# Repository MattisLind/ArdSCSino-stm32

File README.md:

# ArdSCSino-stm32

The idea and the base code was taken from a project created by Tambo (TNB Seisakusho) (https://twitter.com/h_koma2) ArdSCSino is hardware that reproduces SCSI devices (hard disks) with arduino.

### Setup

I am using Arduino Software (IDE) V1.8.13.
Tools-> Boards-> Board Manager-> Search Filters Search and install "Arduino SAM board (32-bit ARM Cortex-M3)" Select the board "Generic STM32F103C series"

I am using the following as a library.

SDFAT (https://github.com/greiman/SdFat/tree/1.1.4) 

* Make sure to use V1 of SdFat (for example V1.1.4 )
* Make sure to set the #define ENABLE_EXTENDED_TRANSFER_CLASS 1 in SdFatConfig.h

Arduino_STM32 (https://github.com/rogerclarkmelbourne/Arduino_STM32/releases/tag/v1.0.0)

## Enhancements

In the STM32SCSISD folder there is a new PCB which integrates the following features:
* Floppy / AMP / TE connectivity connector.
* Pin headers for serial port, USB, SWD connectors. The use of these are for debugging only and is purely optional.
* Jumpers for RESET and BOOT. Also only needed for debuging.
* Jumpers for and image select. The image select feature allow for selecting one out of four images on the card when the SCSI device is selected.
* Jumpers for unit select. Allow the settig of the SCSI ID. The ID is also used to select one of seven sets of images as defined by the image select above.
* Activity LED pin header.
* Mounting holes.

The firmware (in STM32SCSISD_FW) has been improved by optimizing how data is transfered to the SCSI port. One SCSI transaction is now 1.2 microsseconds and the innerloop consists of 30 instructions. Please make sure that you use -O3 optimizations when compiling the project.

```
arm-none-eabi-g++ -mcpu=cortex-m3 -mthumb ArdSCSinoV2.cpp ../../SdFat/src/FatLib/FatFile.cpp  -I../../Arduino_STM32/STM32F1/libraries/SPI/src/ -I../../Arduino_STM32/STM32F1/system/libmaple/include/ -I../../Arduino_STM32/STM32F1/system/libmaple/ -I../../Arduino_STM32/STM32F1/cores/maple/ -I../../Arduino_STM32/STM32F1/variants/generic_stm32f103c -DMCU_STM32F103C8 -I../../Arduino_STM32/STM32F1/system/libmaple/stm32f1/include/ -I../../SdFat/src/ -DARDUINO -DF_CPU=72000000 -D__arm__ -D__STM32F1__ -Dnullptr=NULL -O3
```

Real life copying of 5 Mbyte file under RT-11 operating system running on a PDP-11/23 CPU takes 23 seconds which is equivalent of 218kbytes/s copying speed. Comparing this with the SCSI2SD v5 adapter gives a 305kbytes/s copying speed. 

The design has also been tested successfully with a Luxor ABC1600 computer.

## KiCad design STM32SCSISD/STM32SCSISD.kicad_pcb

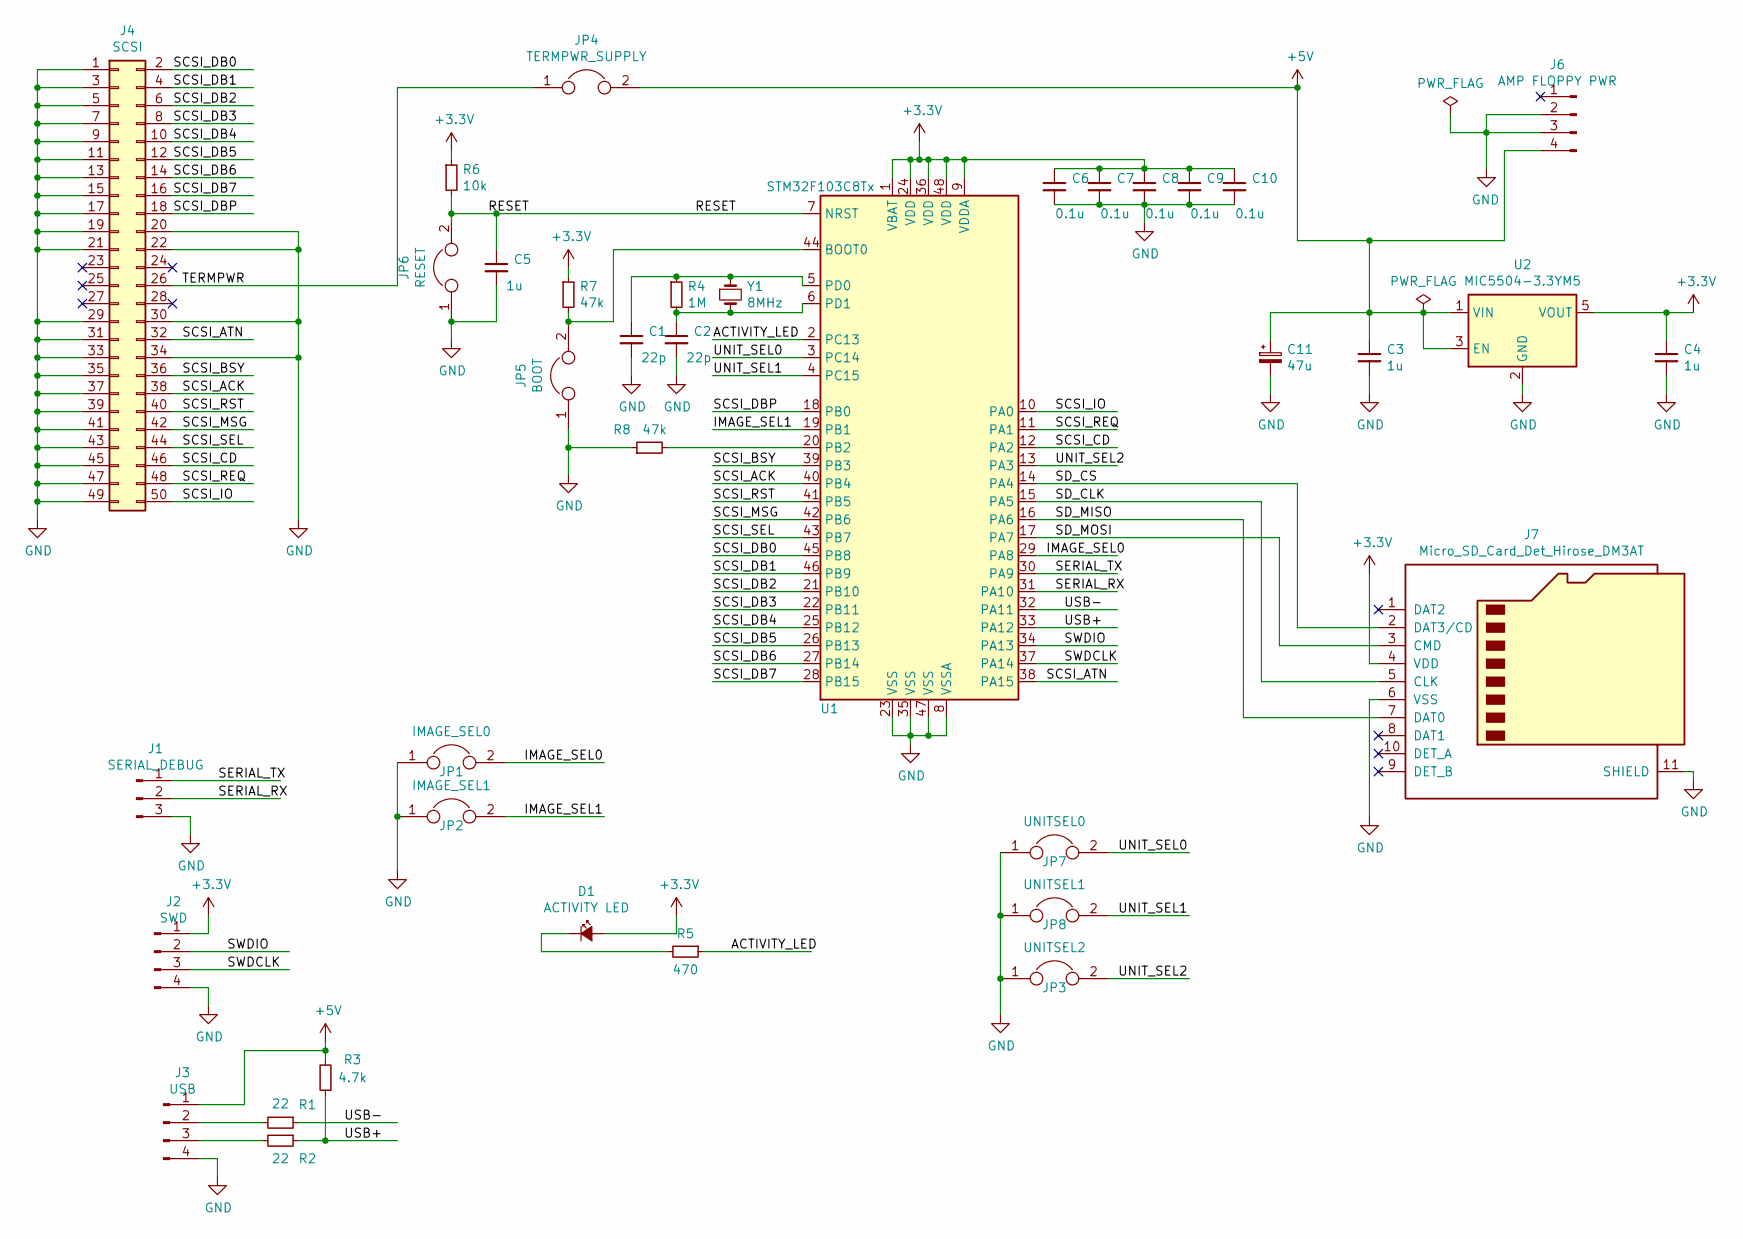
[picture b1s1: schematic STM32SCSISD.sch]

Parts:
C1, C2: 22p; C_0805_2012Metric
C3, C4, C5: 1u; C_0805_2012Metric
C6, C7, C8, C9, C10: 0.1u; C_0805_2012Metric
C11: 47u; CP_Radial_D5.0mm_P2.50mm
D1: ACTIVITY LED; LED_D5.0mm
J1: SERIAL_DEBUG; PinHeader_1x03_P2.54mm_Vertical
J2: SWD; PinHeader_1x04_P2.54mm_Vertical
J3: USB; PinHeader_1x04_P2.54mm_Vertical
J4: SCSI; IDC-Header_2x25_P2.54mm_Vertical
J6: AMP FLOPPY PWR; TE_MATE-N-LOK_350211-1_1x04_P5.08mm_Vertical
J7: Micro_SD_Card_Det_Hirose_DM3AT; microSD_HC_Hirose_DM3AT-SF-PEJM5
JP1: IMAGE_SEL0; PinHeader_1x02_P2.54mm_Vertical
JP2: IMAGE_SEL1; PinHeader_1x02_P2.54mm_Vertical
JP3: UNITSEL2; PinHeader_1x02_P2.54mm_Vertical
JP4: TERMPWR_SUPPLY; PinHeader_1x02_P2.54mm_Vertical
JP5: BOOT; PinHeader_1x02_P2.54mm_Vertical
JP6: RESET; PinHeader_1x02_P2.54mm_Vertical
JP7: UNITSEL0; PinHeader_1x02_P2.54mm_Vertical
JP8: UNITSEL1; PinHeader_1x02_P2.54mm_Vertical
R1, R2: 22; R_0805_2012Metric_Pad1.15x1.40mm_HandSolder
R3: 4.7k; R_0805_2012Metric_Pad1.15x1.40mm_HandSolder
R4: 1M; R_0805_2012Metric_Pad1.15x1.40mm_HandSolder
R5: 470; R_0805_2012Metric_Pad1.15x1.40mm_HandSolder
R6: 10k; R_0805_2012Metric_Pad1.15x1.40mm_HandSolder
R7, R8: 47k; R_0805_2012Metric_Pad1.15x1.40mm_HandSolder
U1: STM32F103C8Tx; LQFP-48_7x7mm_P0.5mm
U2: MIC5504-3.3YM5; SOT-23-5
Y1: 8MHz; Crystal_HC49-U_Vertical

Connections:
+3V3: C4.1, C6.1, C7.1, C8.1, C9.1, C10.1, D1.2 (A), J2.1, J7.4 (VDD), R6.1, R7.1, U1.1 (VBAT), U1.9 (VDDA), U1.24 (VDD), U1.36 (VDD), U1.48 (VDD), U2.5 (VOUT)
+5V: C3.1, C11.1, J3.1, J6.4, JP4.2, R3.2, U2.1 (VIN), U2.3 (EN)
/ACTIVITY_LED: R5.1, U1.2 (PC13)
/IMAGE_SEL0: JP1.2, U1.29 (PA8)
/IMAGE_SEL1: JP2.2, U1.19 (PB1)
/RESET: C5.1, JP6.2, R6.2, U1.7 (NRST)
/SCSI_ACK: J4.38, U1.40 (PB4)
/SCSI_ATN: J4.32, U1.38 (PA15)
/SCSI_BSY: J4.36, U1.39 (PB3)
/SCSI_CD: J4.46, U1.12 (PA2)
/SCSI_DB0: J4.2, U1.45 (PB8)
/SCSI_DB1: J4.4, U1.46 (PB9)
/SCSI_DB2: J4.6, U1.21 (PB10)
/SCSI_DB3: J4.8, U1.22 (PB11)
/SCSI_DB4: J4.10, U1.25 (PB12)
/SCSI_DB5: J4.12, U1.26 (PB13)
/SCSI_DB6: J4.14, U1.27 (PB14)
/SCSI_DB7: J4.16, U1.28 (PB15)
/SCSI_DBP: J4.18, U1.18 (PB0)
/SCSI_IO: J4.50, U1.10 (PA0)
/SCSI_MSG: J4.42, U1.42 (PB6)
/SCSI_REQ: J4.48, U1.11 (PA1)
/SCSI_RST: J4.40, U1.41 (PB5)
/SCSI_SEL: J4.44, U1.43 (PB7)
/SD_CLK: J7.5 (CLK), U1.15 (PA5)
/SD_CS: J7.2 (DAT3/CD), U1.14 (PA4)
/SD_MISO: J7.7 (DAT0), U1.16 (PA6)
/SD_MOSI: J7.3 (CMD), U1.17 (PA7)
/SERIAL_RX: J1.2, U1.31 (PA10)
/SERIAL_TX: J1.1, U1.30 (PA9)
/SWDCLK: J2.3, U1.37 (PA14)
/SWDIO: J2.2, U1.34 (PA13)
/TERMPWR: J4.26, JP4.1
/UNIT_SEL0: JP7.2, U1.3 (PC14)
/UNIT_SEL1: JP8.2, U1.4 (PC15)
/UNIT_SEL2: JP3.2, U1.13 (PA3)
/USB+: R2.1, R3.1, U1.33 (PA12)
/USB-: R1.1, U1.32 (PA11)
GND: C1.2, C2.2, C3.2, C4.2, C5.2, C6.2, C7.2, C8.2, C9.2, C10.2, C11.2, J1.3, J2.4, J3.4, J4.1, J4.3, J4.5, J4.7, J4.9, J4.11, J4.13, J4.15, J4.17, J4.19, J4.20, J4.21, J4.22, J4.29, J4.30, J4.31, J4.33, J4.34, J4.35, J4.37, J4.39, J4.41, J4.43, J4.45, J4.47, J4.49, J6.2, J6.3, J7.6 (VSS), J7.11 (SHIELD), JP1.1, JP2.1, JP3.1, JP5.1, JP6.1, JP7.1, JP8.1, R8.1, U1.8 (VSSA), U1.23 (VSS), U1.35 (VSS), U1.47 (VSS), U2.2 (GND)
unnamed: C1.1, R4.1, U1.5 (PD0), Y1.1
unnamed: C2.1, R4.2, U1.6 (PD1), Y1.2
unnamed: D1.1 (K), R5.2
unnamed: J3.2, R1.2
unnamed: J3.3, R2.2
unnamed: JP5.2, R7.2, U1.44 (BOOT0)
unnamed: R8.2, U1.20 (PB2)

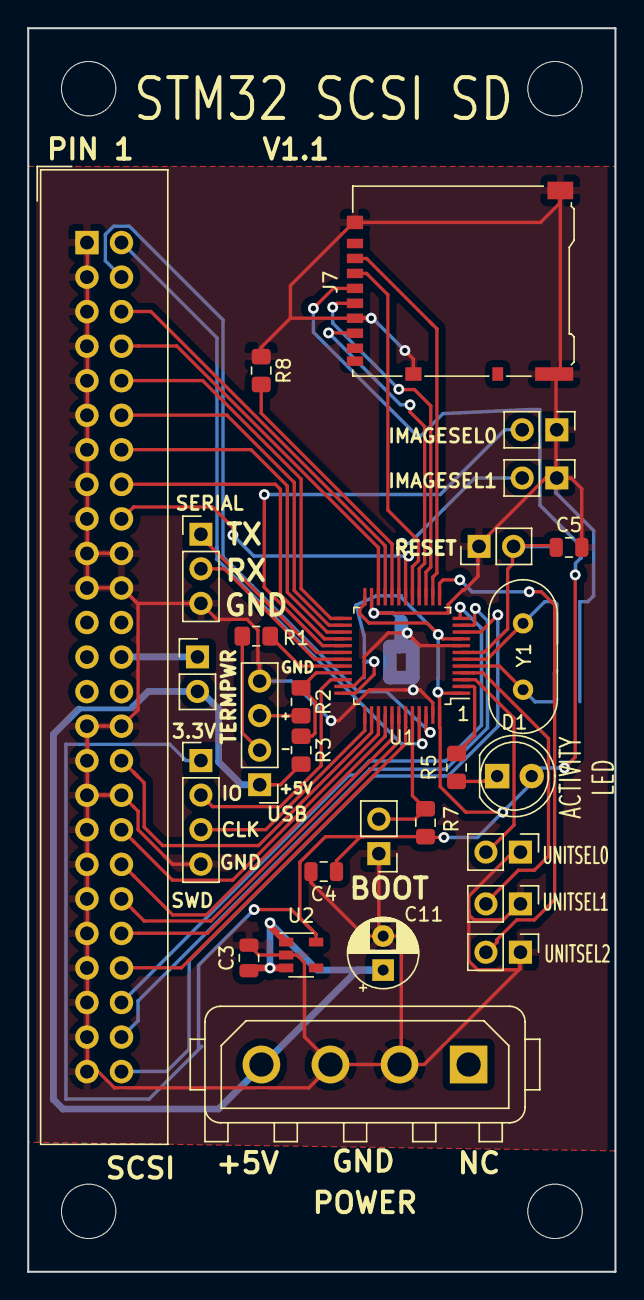
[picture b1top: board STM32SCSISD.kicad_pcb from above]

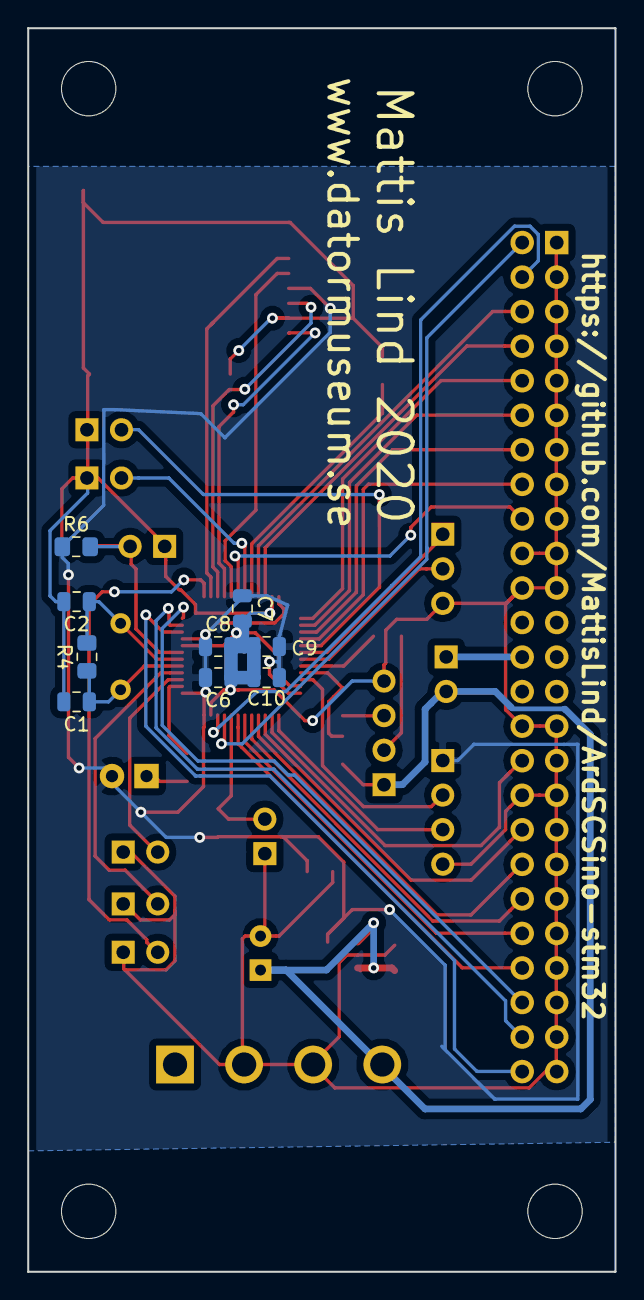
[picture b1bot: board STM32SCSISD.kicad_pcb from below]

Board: 2 copper layers, 43.2 x 91.4 mm, 37 parts (9 on the bottom side), 46 nets.

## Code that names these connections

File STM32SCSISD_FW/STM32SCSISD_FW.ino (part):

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#define gpio_write(pin,val) gpio_write_bit(PIN_MAP[pin].gpio_device, PIN_MAP[pin].gpio_bit, val)
#define gpio_read(pin) gpio_read_bit(PIN_MAP[pin].gpio_device, PIN_MAP[pin].gpio_bit)

//#define DB0       PB8     // SCSI:DB0
//#define DB1       PB9     // SCSI:DB1
//#define DB2       PB10    // SCSI:DB2
//#define DB3       PB11    // SCSI:DB3
//#define DB4       PB12    // SCSI:DB4
//#define DB5       PB13    // SCSI:DB5
//#define DB6       PB14    // SCSI:DB6
//#define DB7       PB15    // SCSI:DB7
//#define DBP       PB0     // SCSI:DBP

#define ATN       PA15      // SCSI:ATN
#define BSY       PB3      // SCSI:BSY
#define ACK       PB4     // SCSI:ACK
#define RST       PB5     // SCSI:RST
#define MSG       PB6      // SCSI:MSG
#define SEL       PB7      // SCSI:SEL
#define CD        PA2      // SCSI:I/O
#define REQ       PA1      // SCSI:REQ
#define IO        PA0      // SCSI:C/D

#define SD_CS     PA4      // SDCARD:CS
#define LED       PC13     // LED

#define UNITSELECT0 PC14
#define UNITSELECT1 PC15
#define UNITSELECT2 PA3
#define IMAGESELECT0 PA8
#define IMAGESELECT1 PB1

int SCSIID;             

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  int i;
  char fullFileName [13];
  fullFileName[0]=0;
  // PA15 / PB3 / PB4 is needed.
  // But only disable JTAG not SWD
  afio_cfg_debug_ports(AFIO_DEBUG_SW_ONLY);
  // Activity LED
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  strcat(fullFileName, imageNo);
  strcat(fullFileName, ".DSK");
  
  GPIOB->regs->CRH = 0x88888888; // SET INPUT W/ PUPD on PB15-PB8
  gpio_mode(UNITSELECT0, GPIO_INPUT_PU);
  gpio_mode(UNITSELECT1, GPIO_INPUT_PU);
  gpio_mode(UNITSELECT2, GPIO_INPUT_PU);
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  gpio_write(MSG, low);
  gpio_write(CD, low);
  gpio_write(IO, high);
  GPIOB->regs->CRL |= 0x00000003; // SET OUTPUT W/ PUPD on PA7-PB0 50MHz
  GPIOB->regs->CRH = 0x33333333; // SET OUTPUT W/ PUPD on PB15-PB8 50MHz
  for (int i = 0; i < len; i++) {
    if(m_isBusReset) {
      return;
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  gpio_write(MSG, low);
  gpio_write(CD, low);
  gpio_write(IO, high);
  GPIOB->regs->CRL |= 0x00000003; // SET OUTPUT W/ PUPD on PA7-PB0 50MHz
  GPIOB->regs->CRH = 0x33333333; // SET OUTPUT W/ PUPD on PB15-PB8 50MHz
  
  for(uint32_t i = 0; i < len; i++) {
    m_file.read(m_buf, BLOCKSIZE);
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  gpio_write(MSG, low);
  gpio_write(CD, low);
  gpio_write(IO, high);
  GPIOB->regs->CRL |= 0x00000003; // SET OUTPUT W/ PUPD on PA7-PB0 50MHz
  GPIOB->regs->CRH = 0x33333333; // SET OUTPUT W/ PUPD on PB15-PB8 50MHz
  for(uint32_t i = 0; i < len; i++) {
    m_file.read(m_buf, BLOCKSIZE);
    for(int j = 0; j < BLOCKSIZE; j++) {
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  gpio_write(MSG, low);
  gpio_write(CD, low);
  gpio_write(IO, low);
  GPIOB->regs->CRH = 0x88888888; // SET INPUT W/ PUPD on PB15-PB8
  for(uint32_t i = 0; i < len; i++) {
  register byte *dstptr= m_buf;
  register byte *endptr= m_buf + BLOCKSIZE;
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  gpio_write(MSG, low);
  gpio_write(CD, low);
  gpio_write(IO, low);
  GPIOB->regs->CRH = 0x88888888; // SET INPUT W/ PUPD on PB15-PB8
  for(uint32_t i = 0; i < len; i++) {
    for(int j = 0; j < BLOCKSIZE; j++) {
      if(m_isBusReset) {
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  gpio_write(MSG, high);
  gpio_write(CD, high);
  gpio_write(IO, high);
  GPIOB->regs->CRL |= 0x00000003; // SET OUTPUT W/ PUPD on PA7-PB0 50MHz
  GPIOB->regs->CRH = 0x33333333; // SET OUTPUT W/ PUPD on PB15-PB8 50MHz
  writeHandshake(msg);
}

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  gpio_write(MSG, high);
  gpio_write(CD, high);
  gpio_write(IO, low);
  GPIOB->regs->CRH = 0x88888888; // SET INPUT W/ PUPD on PB15-PB8
  m_msb[m_msc] = readHandshake();
  m_msc++;
  m_msc %= 256;
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    return;
  }
  // BSY+ SEL-
  GPIOB->regs->CRH = 0x88888888; // SET INPUT W/ PUPD on PB15-PB8
  byte db = readIO();  
  LOGN("SELECTION");
  LOGHEX(db);
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  gpio_write(IO, low);
  int len;
  byte cmd[12];
  GPIOB->regs->CRH = 0x88888888; // SET INPUT W/ PUPD on PB15-PB8
  cmd[0] = readHandshake();
  LOGHEX(cmd[0]);
  len = 1;
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  default:
    break;
  }
  GPIOB->regs->CRH = 0x88888888; // SET INPUT W/ PUPD on PB15-PB8
  for(int i = 1; i < len; i++ ) {
    cmd[i] = readHandshake();
    LOGHEX(cmd[i]);
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  gpio_write(MSG, low);
  gpio_write(CD, high);
  gpio_write(IO, high);
  GPIOB->regs->CRL |= 0x00000003; // SET OUTPUT W/ PUPD on PA7-PB0 50MHz
  GPIOB->regs->CRH = 0x33333333; // SET OUTPUT W/ PUPD on PB15-PB8 50MHz
  writeHandshake(sts);
  if(m_isBusReset) {
     goto BusFree;
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  gpio_write(MSG, high);
  gpio_write(CD, high);
  gpio_write(IO, high);
  GPIOB->regs->CRL |= 0x00000003; // SET OUTPUT W/ PUPD on PA7-PB0 50MHz
  GPIOB->regs->CRH = 0x33333333; // SET OUTPUT W/ PUPD on PB15-PB8 50MHz
  writeHandshake(msg);

BusFree:
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
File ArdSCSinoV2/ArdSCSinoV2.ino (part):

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#define gpio_write(pin,val) gpio_write_bit(PIN_MAP[pin].gpio_device, PIN_MAP[pin].gpio_bit, val)
#define gpio_read(pin) gpio_read_bit(PIN_MAP[pin].gpio_device, PIN_MAP[pin].gpio_bit)

//#define DB0       PB8     // SCSI:DB0
//#define DB1       PB9     // SCSI:DB1
//#define DB2       PB10    // SCSI:DB2
//#define DB3       PB11    // SCSI:DB3
//#define DB4       PB12    // SCSI:DB4
//#define DB5       PB13    // SCSI:DB5
//#define DB6       PB14    // SCSI:DB6
//#define DB7       PB15    // SCSI:DB7
//#define DBP       PB0     // SCSI:DBP

#define ATN       PA8      // SCSI:ATN
#define BSY       PA9      // SCSI:BSY
#define ACK       PA10     // SCSI:ACK
#define RST       PA15     // SCSI:RST
#define MSG       PB3      // SCSI:MSG
#define SEL       PB4      // SCSI:SEL
#define CD        PB5      // SCSI:C/D
#define REQ       PB6      // SCSI:REQ
#define IO        PB7      // SCSI:I/O

#define SD_CS     PA4      // SDCARD:CS
#define LED       PC13     // LED

// GPIOレジスタポート
#define PAREG GPIOA->regs
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{
  //GPIO(SCSI BUS)初期化
  //ポート設定レジスタ（下位）
//  GPIOB->regs->CRL |= 0x000000008; // SET INPUT W/ PUPD on PAB-PB0
  //ポート設定レジスタ（上位）
  
//  GPIOB->regs->ODR = 0x0000FF00; // SET PULL-UPs on PB15-PB8
  //ポート入力データレジスタ
/*  uint32 ret = GPIOB->regs->IDR;
  byte bret =  0x00;
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{
  //GPIO(SCSI BUS)初期化
  //ポート設定レジスタ（下位）
//  GPIOB->regs->ODR != 0x0000FF00; // SET PULL-UPs on PB15-PB8
/*  LOGHEXN((v));
  LOGHEXN((GPIOB->regs->ODR & 0x00ff));
  LOGHEXN((  (GPIOB->regs->ODR & 0x00ff) | (0xff00 & (v <<8)))); */
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 */
void setup()
{
  // PA15 / PB3 / PB4 が使えない
  // But only disable JTAG not SWD
  afio_cfg_debug_ports(AFIO_DEBUG_SW_ONLY);

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
 //GPIO(SCSI BUS)初期化
  //ポート設定レジスタ（下位）
//  GPIOB->regs->CRL |= 0x000000008; // SET INPUT W/ PUPD on PAB-PB0
  //ポート設定レジスタ（上位）
  GPIOB->regs->CRH = 0x88888888; // SET INPUT W/ PUPD on PB15-PB8
//  GPIOB->regs->ODR = 0x0000FF00; // SET PULL-UPs on PB15-PB8

  gpio_mode(ATN, GPIO_INPUT_PU);
  gpio_mode(BSY, GPIO_INPUT_PU);
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  gpio_write(MSG, low);
  gpio_write(CD, low);
  gpio_write(IO, high);
  GPIOB->regs->CRL |= 0x00000003; // SET OUTPUT W/ PUPD on PA7-PB0 50MHz
  //ポート設定レジスタ（上位）
  GPIOB->regs->CRH = 0x33333333; // SET OUTPUT W/ PUPD on PB15-PB8 50MHz

  for (int i = 0; i < len; i++) {
    if(m_isBusReset) {
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  gpio_write(MSG, low);
  gpio_write(CD, low);
  gpio_write(IO, high);
  GPIOB->regs->CRL |= 0x00000003; // SET OUTPUT W/ PUPD on PA7-PB0 50MHz
  GPIOB->regs->CRH = 0x33333333; // SET OUTPUT W/ PUPD on PB15-PB8 50MHz
  
  for(uint32_t i = 0; i < len; i++) {
    m_file.read(m_buf, BLOCKSIZE);
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  SCSI_OUT(vMSG,inactive) //  gpio_write(MSG, low);
  SCSI_OUT(vCD ,inactive) //  gpio_write(CD, low);
  SCSI_OUT(vIO ,inactive) //  gpio_write(IO, low);
  GPIOB->regs->CRH = 0x88888888; // SET INPUT W/ PUPD on PB15-PB8
  for(uint32_t i = 0; i < len; i++) {
  register byte *dstptr= m_buf;
  register byte *endptr= m_buf + BLOCKSIZE;
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  gpio_write(MSG, low);
  gpio_write(CD, low);
  gpio_write(IO, low);
  GPIOB->regs->CRH = 0x88888888; // SET INPUT W/ PUPD on PB15-PB8
  for(uint32_t i = 0; i < len; i++) {
    for(int j = 0; j < BLOCKSIZE; j++) {
      if(m_isBusReset) {
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  gpio_write(MSG, high);
  gpio_write(CD, high);
  gpio_write(IO, high);
    GPIOB->regs->CRL |= 0x00000003; // SET OUTPUT W/ PUPD on PA7-PB0 50MHz
  //ポート設定レジスタ（上位）
  GPIOB->regs->CRH = 0x33333333; // SET OUTPUT W/ PUPD on PB15-PB8 50MHz

  writeHandshake(msg);
}
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  gpio_write(MSG, high);
  gpio_write(CD, high);
  gpio_write(IO, low);
  GPIOB->regs->CRH = 0x88888888; // SET INPUT W/ PUPD on PB15-PB8
  m_msb[m_msc] = readHandshake();
  m_msc++;
  m_msc %= 256;
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    return;
  }
  // BSY+ SEL-
  GPIOB->regs->CRH = 0x88888888; // SET INPUT W/ PUPD on PB15-PB8
  byte db = readIO();  
  if((db & (1 << SCSIID)) == 0) {
    return;
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  gpio_write(MSG, low);
  gpio_write(CD, high);
  gpio_write(IO, low);
  GPIOB->regs->CRH = 0x88888888; // SET INPUT W/ PUPD on PB15-PB8
  int len;
  byte cmd[12];
  cmd[0] = readHandshake();
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  default:
    break;
  }
  GPIOB->regs->CRH = 0x88888888; // SET INPUT W/ PUPD on PB15-PB8
  for(int i = 1; i < len; i++ ) {
    cmd[i] = readHandshake();
    LOGHEX(cmd[i]);
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  gpio_write(MSG, low);
  gpio_write(CD, high);
  gpio_write(IO, high);
    GPIOB->regs->CRL |= 0x00000003; // SET OUTPUT W/ PUPD on PA7-PB0 50MHz
  //ポート設定レジスタ（上位）
  GPIOB->regs->CRH = 0x33333333; // SET OUTPUT W/ PUPD on PB15-PB8 50MHz

  writeHandshake(sts);
  if(m_isBusReset) {
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  gpio_write(MSG, high);
  gpio_write(CD, high);
  gpio_write(IO, high);
    GPIOB->regs->CRL |= 0x00000003; // SET OUTPUT W/ PUPD on PA7-PB0 50MHz
  //ポート設定レジスタ（上位）
  GPIOB->regs->CRH = 0x33333333; // SET OUTPUT W/ PUPD on PB15-PB8 50MHz

  writeHandshake(msg);

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
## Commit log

2020-11-26 Moved file and enabaled SWD debug while JTAG remained turned off to allow for ST-LINK programming.
2020-11-28 Started designing a new PCB.
2020-11-29 Pre-review of schematic.
2020-11-29 Added a modified firmware adapted to the new PCB.
2020-12-01 Plenty of optimizations.
2020-12-01 More optimizations.
2020-12-04 Hope this board looks nice!
2020-12-26 Simple test software that loops all signals to check for soldering errors
2020-12-26 First version that worked on the new hardware. Two datasignals was interchanged by mistake and required a software change.
2020-12-26 Changed hardware to fix the problem instead since it is best longterm.
2020-12-26 Optimized reading from SCSI bus.
2020-12-26 Optimized writing to SCSI bus as well.
2020-12-26 Further optimzing writeHandshake
2020-12-26 Blinking LED due to different error conditions and once when starting.
2020-12-27 Added ifdef for DEBUG and parity.
2020-12-27 Fixed the two SCSI databus bit that was mixed up. Added a 5mm LED instead of connector.
2020-12-27 Fixed the layout so that now it in sync with schematic. DB0 and DB1 is now corrected.
2020-12-27 Moved the mounting holes a bit and made sure the filled area didn't enter the area of the mounting holes.
2020-12-27 Added support for unit and image selection via jumpers.
2020-12-29 Testing optimizations. New WritePhaseSD creates an instability which refuses it to read correctly some times. Going back to old code always work
2020-12-30 More 7.5us for 8 transactions. Better than 1 MBytes/s!
2020-12-30 Loop unroll four transactions per loop.
2020-12-30 Checking busreset in a diferent way. Saved 360ns over 8 cycles. Now 7.1 us for 8 cycles.
2020-12-30 Reordering decrease time for 8 cycles down to 6.7us
2020-12-30 8 transaction and added one missing handlimg of busreset. Down to 5.6 us for 8 cycles
2020-12-30 Massive unrolling and weird macros. Now at more than 1.5 Mbyte/s!
2020-12-30 Added more optimzations to write as well. Now down to 18 second copying a 5 meg file on RT-11.
2021-03-02 Tester has better documentation.
2021-03-02 This version is running on ABC1600.
2021-03-03 Removed REQ bitmask from Macro since it was unecessary. Partity is on PB0 not PA8.
2021-03-03 Added version 1.1 in the silkscreen.
2021-03-03 New pdf file to better reflect actual design. PB0 is parity.
2021-06-23 Supporting SUN 3/60 required some small mods.
